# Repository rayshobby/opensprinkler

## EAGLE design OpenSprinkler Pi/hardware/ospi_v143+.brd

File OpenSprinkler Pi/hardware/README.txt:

OpenSprinkler Pi (OSPi) Eagle Design Files
==========================================
Note: requires Eagle CAD v6.0 or above

Part lists of all versions can be found at:
http://goo.gl/4Nrvb

Release Notes
=============
New in v1.43+
* Removed on-board relay. Replaced by a header for RF transmitter.
* Added PCB spark gaps.
* Added laser cut acrylic enclosure design (in EagleCAD file, this is
  at layer 113. A .ai file is also provided).

New in v1.4 / v1.4 B+
* New layout to fit the OpenSprinkler injection-molded enclosure
* Changed on-board relay to 250V / 3A type

New in v1.3
* Added per-station bidirectional TVS (SMBJ48CA)
* Added 2A solder-on fuse
* Added on-board mini-relay (120V / 2A)
* Added rain sensor terminal
* 24V AC terminal block changed to orange 3.96 spacing type

New in v1.2
* Added PCF8591T 8-bit 4-channel ADC (analog-digital converter)
* Added pin headers for ADC and also i2C pins.

New in v1.1
-----------
* Adopt LM2596S-5.0 as switching regulator, less peripheral elements, more output current.
* Improved locations of the separation pillars to fit both RPi rev. 1 and rev. 2.
  There are now two pillars that match the screw hole locations on rev. 2 .
* Changed 32.768kHz crystal to SMT package.
* Changed the value of D1 to S1B type.

Original Release v1.0
---------------------
- MC34063 switching regulator.
- DS1307 RTC with CR1220 backup battery.
- Shift register, BT1308W triac solenoid driver.

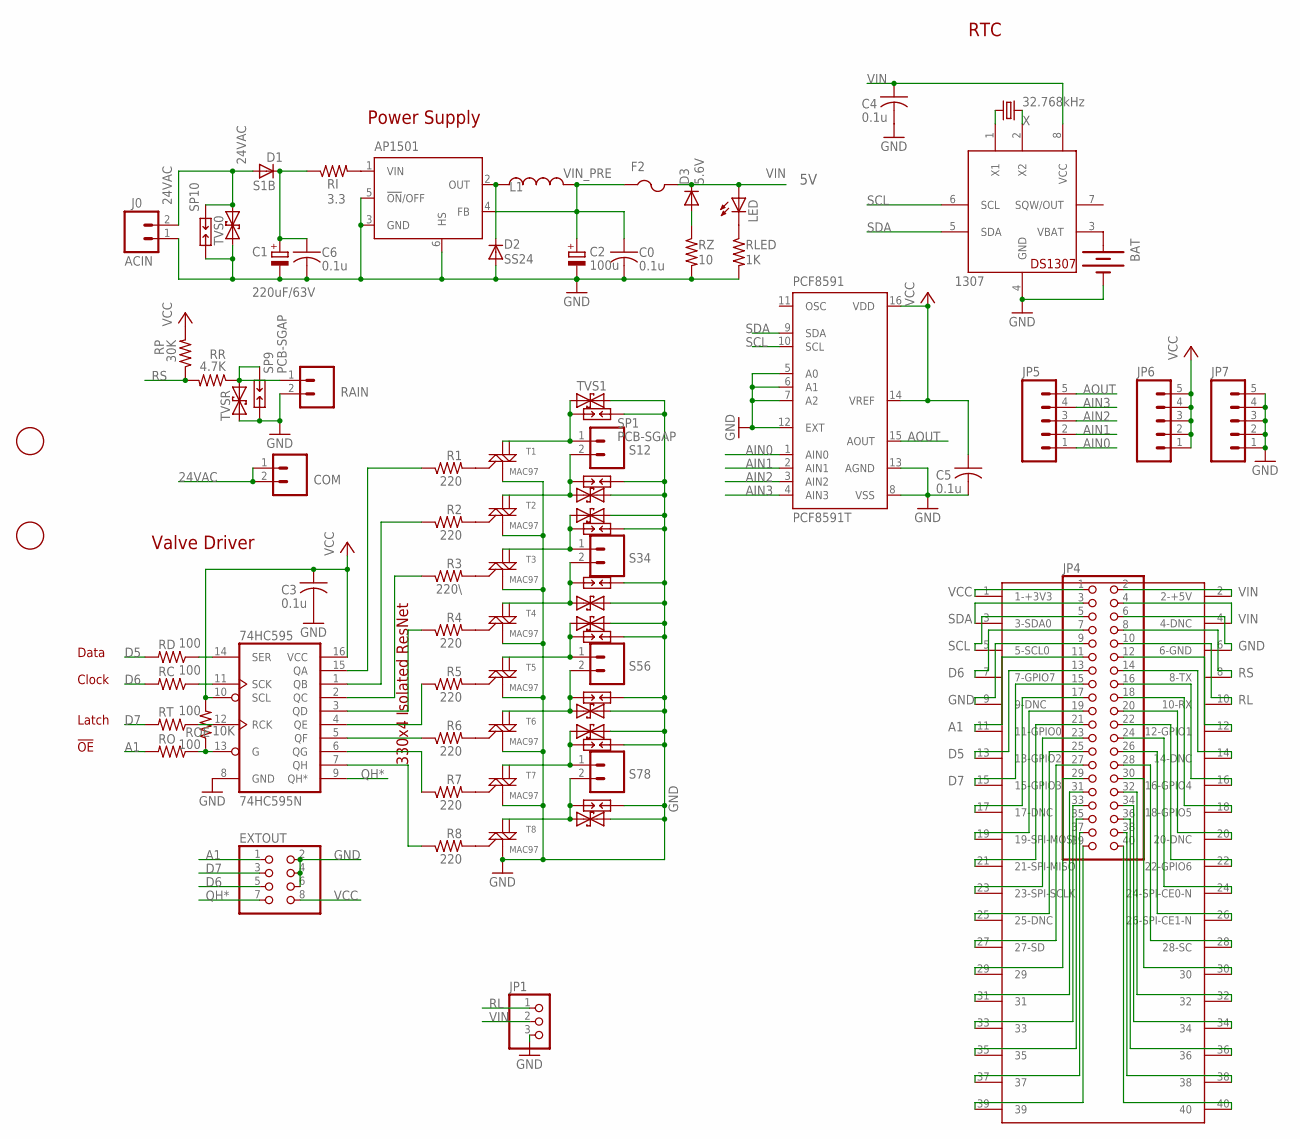
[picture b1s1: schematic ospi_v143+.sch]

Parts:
74HC595: 74HC595N; SO16
1307: DS1307; SO08
AP1501: LM2596S; TO263-5
BAT: BATTERYBATTERY_12MM_SMT; BATTCON_12MM_SMT
C0, C3, C4, C5, C6: 0.1u; C0603K
C1: 220uF/63V; PANASONIC_E
C2: 100u; PANASONIC_E
COM: M025MM-X; SCREWTERMINAL-5MM-2-X
D1: S1B; DO-214AC
D2: SS24; SMB
D3: 5.6V; MINIMELF
EXTOUT: PINHD-2X4/90; 2X04/90
F2: PTCFUSE-1812; 1812
J0: ACIN; SCREWTERMINAL-4MM-2-X
JP1: PINHD-1X3; 1X03
JP4: PINHD-2X20; 2X20
JP5, JP6, JP7: M05PTH; 1X05
L1: 150uH; CDRH125
LED: LEDCHIPLED_0805; CHIPLED_0805
PCF8591: PCF8591T; SO16W
R1, R2, R4, R5, R6, R7, R8: 220; R0603
R3: 220\; R0603
RAIN: M025MM-X; SCREWTERMINAL-5MM-2-X
RC: 100; R0603
RD: 100; R0603
RI: 3.3; R2010
RLED: 1K; R0805
RO: 100; R0603
ROE: 10K; R0603
RP: 30K; R0805
RR: 4.7K; R0805
RT: 100; R0603
RZ: 10; R2010
S12, S34, S56, S78: M025MM-X; SCREWTERMINAL-5MM-2-X
SP1, SP2, SP3, SP4, SP5, SP6, SP7, SP8, SP9, SP10: PCB-SGAP
T1, T2, T3, T4, T5, T6, T7, T8: MAC97; SOT223
TVS0, TVS1, TVS2, TVS3, TVS4, TVS5, TVS6, TVS7, TVS8: TVSSMB; SMB
TVSR: TVSSMB; SMB
U$1, U$3: FIDUCIAL; FIDUCIAL_1MM
U$2: RPIB+
X: 32.768kHz; MM20SS

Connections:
24VAC: COM.1, COM.2, D1.A, J0.2, SP10.1, TVS0.C
A1: EXTOUT.1, JP4.11, RO.2, U$2.11 (11-GPIO0)
AIN0: JP5.1, PCF8591.1 (AIN0)
AIN1: JP5.2, PCF8591.2 (AIN1)
AIN2: JP5.3, PCF8591.3 (AIN2)
AIN3: JP5.4, PCF8591.4 (AIN3)
AOUT: JP5.5, PCF8591.15 (AOUT)
D5: JP4.13, RD.2, U$2.13 (13-GPIO2)
D6: EXTOUT.5, JP4.7, RC.2, U$2.7 (7-GPIO7)
D7: EXTOUT.3, JP4.15, RT.2, U$2.15 (15-GPIO3)
GND: 74HC595.8 (GND), 1307.4 (GND), AP1501.3 (GND), AP1501.5 (!ON!/OFF), AP1501.6 (HS), BAT.P$1 (-), C0.2, C1.-, C2.-, C3.2, C4.2, C5.2, C6.2, D2.A, EXTOUT.2, EXTOUT.4, EXTOUT.6, J0.1, JP1.3, JP4.6, JP4.9, JP7.1, JP7.2, JP7.3, JP7.4, JP7.5, PCF8591.5 (A0), PCF8591.6 (A1), PCF8591.7 (A2), PCF8591.8 (VSS), PCF8591.12 (EXT), PCF8591.13 (AGND), RAIN.2, RLED.2, RZ.2, SP1.1, SP2.1, SP3.1, SP4.1, SP5.1, SP6.1, SP7.1, SP8.1, SP9.2, SP10.2, T1.1 (M1), T2.1 (M1), T3.1 (M1), T4.1 (M1), T5.1 (M1), T6.1 (M1), T7.1 (M1), T8.1 (M1), TVS0.A, TVS1.C, TVS2.C, TVS3.C, TVS4.C, TVS5.C, TVS6.C, TVS7.C, TVS8.C, TVSR.A, U$2.6 (6-GND), U$2.9 (9-DNC)
unnamed: LED.C, RLED.1
unnamed: C1.+, C6.1, D1.C, RI.1
unnamed: R1.2, T1.3 (G)
unnamed: 74HC595.5 (QF), R6.1
unnamed: 74HC595.6 (QG), R7.1
unnamed: D3.A, RZ.1
unnamed: 74HC595.7 (QH), R8.1
unnamed: AP1501.2 (OUT), D2.C, L1.1
unnamed: 1307.2 (X2), X.4 (2)
unnamed: 74HC595.4 (QE), R5.1
unnamed: 74HC595.3 (QD), R4.1
unnamed: 74HC595.2 (QC), R3.1
unnamed: 74HC595.1 (QB), R2.1
unnamed: 74HC595.15 (QA), R1.1
unnamed: R2.2, T2.3 (G)
unnamed: S12.1, SP1.2, T1.2 (M2), TVS1.A
unnamed: S12.2, SP2.2, T2.2 (M2), TVS2.A
unnamed: S34.1, SP3.2, T3.2 (M2), TVS3.A
unnamed: R3.2, T3.3 (G)
unnamed: S34.2, SP4.2, T4.2 (M2), TVS4.A
unnamed: R4.2, T4.3 (G)
unnamed: S56.1, SP5.2, T5.2 (M2), TVS5.A
unnamed: S56.2, SP6.2, T6.2 (M2), TVS6.A
unnamed: S78.1, SP7.2, T7.2 (M2), TVS7.A
unnamed: S78.2, SP8.2, T8.2 (M2), TVS8.A
unnamed: R5.2, T5.3 (G)
unnamed: R6.2, T6.3 (G)
unnamed: R7.2, T7.3 (G)
unnamed: R8.2, T8.3 (G)
unnamed: 1307.1 (X1), X.1
unnamed: RAIN.1, RR.1, SP9.1, TVSR.C
unnamed: 74HC595.14 (SER), RD.1
unnamed: 74HC595.11 (SCK), RC.1
unnamed: 74HC595.12 (RCK), RT.1
unnamed: 1307.3 (VBAT), BAT.P$2 (+)
unnamed: JP4.12, U$2.12 (12-GPIO1)
unnamed: JP4.14, U$2.14 (14-DNC)
unnamed: JP4.16, U$2.16 (16-GPIO4)
unnamed: 74HC595.13 (G), RO.1, ROE.1
unnamed: JP4.23, U$2.23 (23-SPI-SCLK)
unnamed: JP4.25, U$2.25 (25-DNC)
unnamed: JP4.27, U$2.27 (27-SD)
unnamed: JP4.29, U$2.29
unnamed: JP4.39, U$2.39
unnamed: JP4.37, U$2.37
unnamed: JP4.17, U$2.17 (17-DNC)
unnamed: JP4.19, U$2.19 (19-SPI-MOSI)
unnamed: JP4.21, U$2.21 (21-SPI-MISO)
unnamed: JP4.35, U$2.35
unnamed: JP4.33, U$2.33
unnamed: JP4.31, U$2.31
unnamed: JP4.34, U$2.34
unnamed: JP4.36, U$2.36
unnamed: JP4.38, U$2.38
unnamed: JP4.40, U$2.40
unnamed: AP1501.1 (VIN), RI.2
unnamed: JP4.18, U$2.18 (18-GPIO5)
unnamed: JP4.20, U$2.20 (20-DNC)
unnamed: JP4.22, U$2.22 (22-GPIO6)
unnamed: JP4.24, U$2.24 (24-SPI-CE0-N)
unnamed: JP4.26, U$2.26 (26-SPI-CE1-N)
unnamed: JP4.28, U$2.28 (28-SC)
unnamed: JP4.30, U$2.30
unnamed: JP4.32, U$2.32
QH*: 74HC595.9 (QH*), EXTOUT.7
RL: JP1.1, JP4.10, U$2.10 (10-RX)
RS: JP4.8, RP.1, RR.2, U$2.8 (8-TX)
SCL: 1307.6 (SCL), JP4.5, PCF8591.10 (SCL), U$2.5 (5-SCL0)
SDA: 1307.5 (SDA), JP4.3, PCF8591.9 (SDA), U$2.3 (3-SDA0)
VCC: 74HC595.10 (SCL), 74HC595.16 (VCC), C3.1, C5.1, EXTOUT.8, JP4.1, JP6.1, JP6.2, JP6.3, JP6.4, JP6.5, PCF8591.14 (VREF), PCF8591.16 (VDD), ROE.2, RP.2, U$2.1 (1-+3V3)
VIN: 1307.8 (VCC), C4.1, D3.C, F2.2, JP1.2, JP4.2, JP4.4, LED.A, U$2.2 (2-+5V), U$2.4 (4-DNC)
VIN_PRE: AP1501.4 (FB), C0.1, C2.+, F2.1, L1.2

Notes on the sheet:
Power Supply
Valve Driver
Data
Clock
Latch
330x4 Isolated ResNet
!OE
RTC

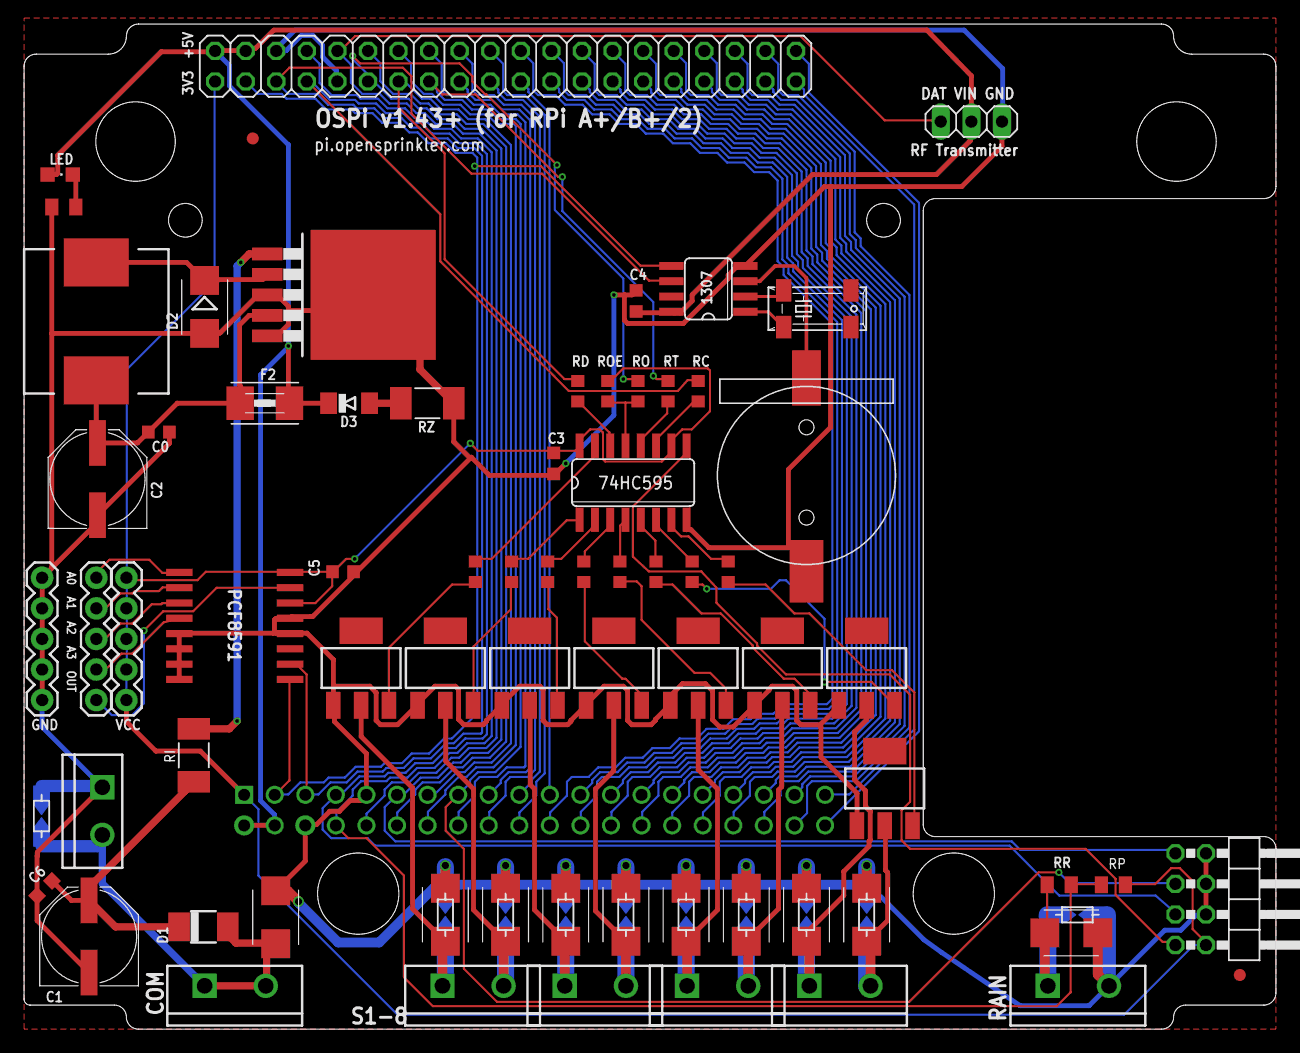
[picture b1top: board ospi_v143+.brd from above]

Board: 2 copper layers, 104.0 x 83.5 mm, 81 parts (1 on the bottom side), 83 nets.

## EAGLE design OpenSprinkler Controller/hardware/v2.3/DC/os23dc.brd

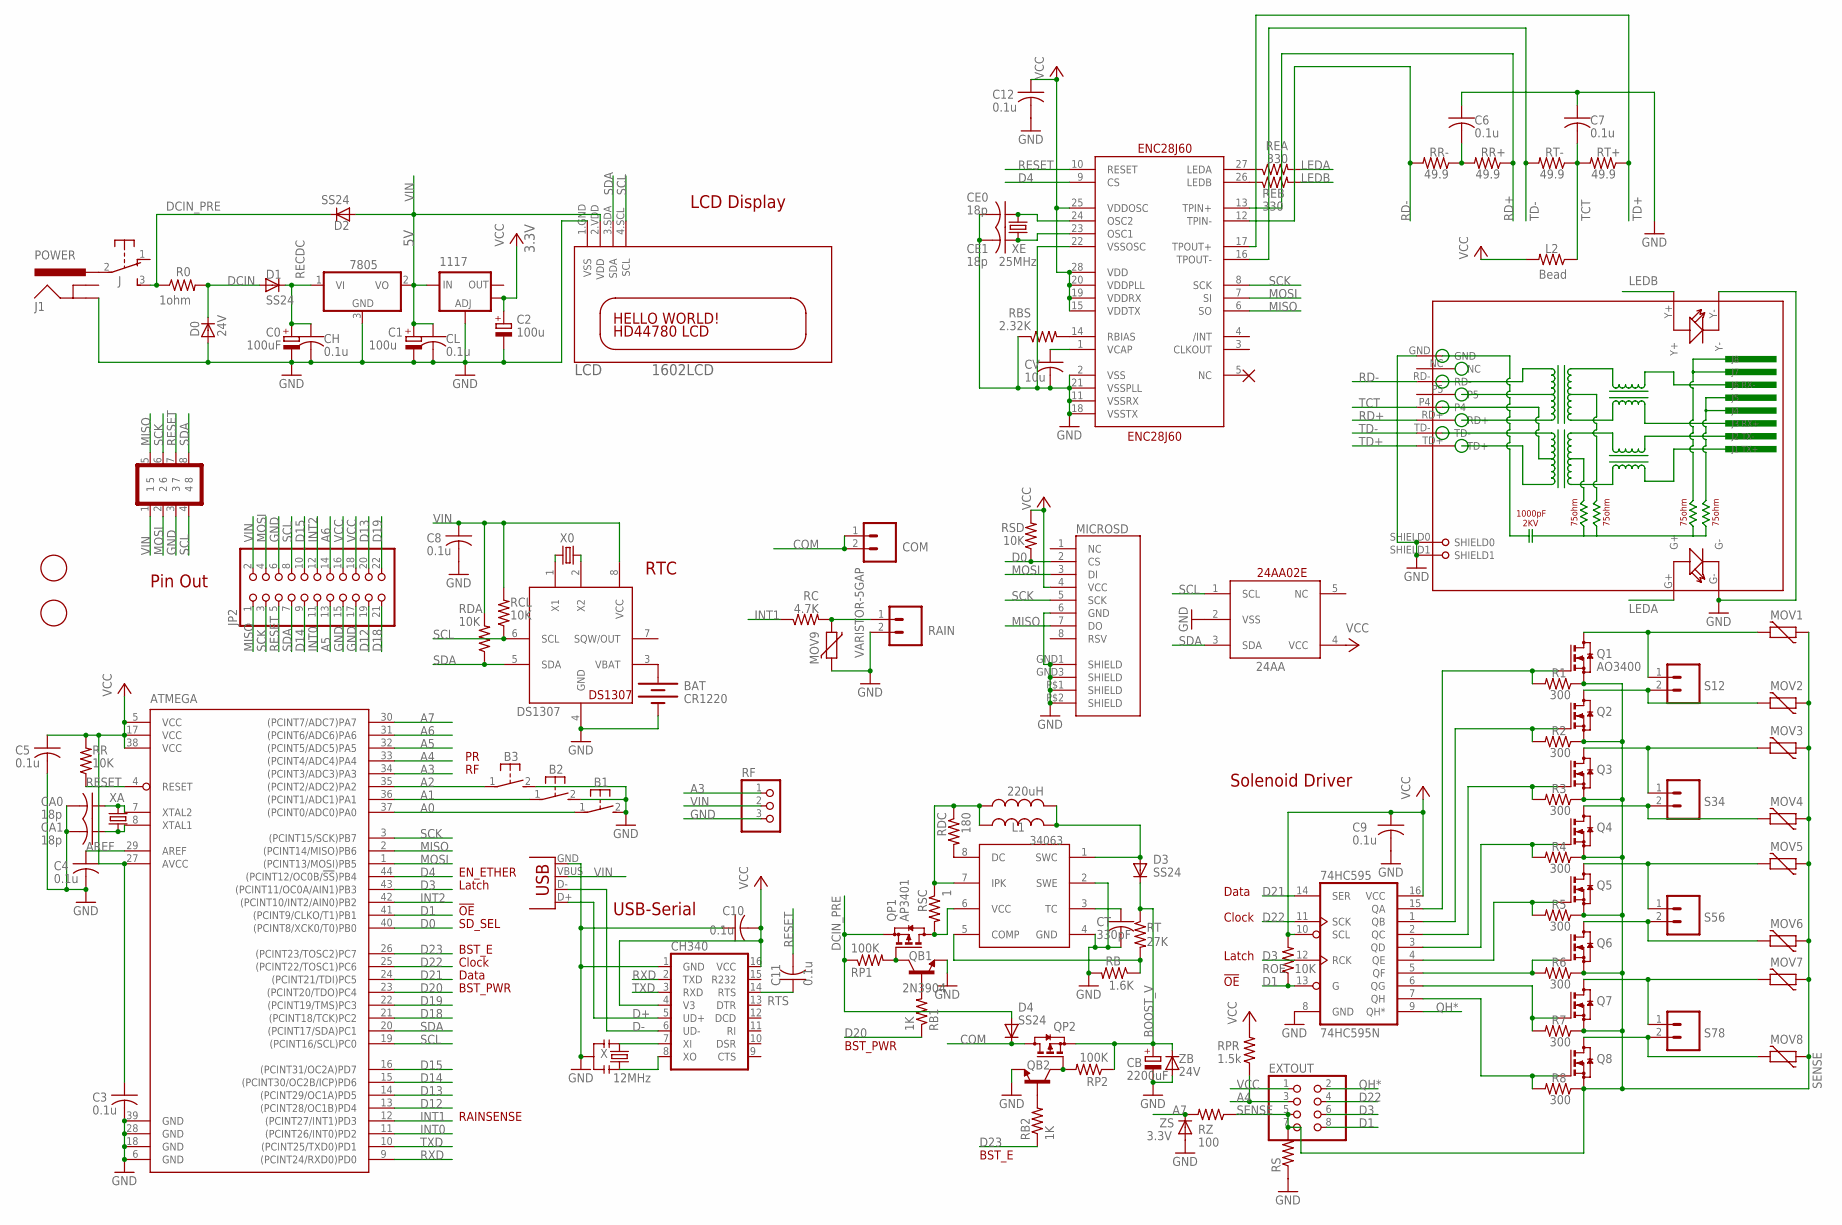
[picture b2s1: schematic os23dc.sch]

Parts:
24AA: 24AA02E48; SOT23-5L
74HC595: 74HC595N; SO16
1117: V_REG_LM1117SOT223; SOT223
7805: 7805DT; TO252
34063: MC33063/MC34063D; SO08
ATMEGA: ATMEGA644A; TQFP44
B1, B2, B3: 31-XX; B3F-31XX
BAT: CR1220; BATTCON_12MM_SMT
C0: 100uF; PANASONIC_E
C1, C2: 100u; PANASONIC_D
C3, C7: 0.1u; C0603K
C4, C5, C6, C8, C9, C10, C11, C12: 0.1u; C0603
CA0, CA1: 18p; C0603K
CB: 2200uF; E7,5-16
CE0, CE1: 18p; C0603K
CH: 0.1u; C0603
CH340: CH340G; SO16
CL: 0.1u; C0603
COM: M025MM-X; SCREWTERMINAL-5MM-2-X
CT: 330pF; C0603K
CV: 10u; C0805K
D0: 24V; MINIMELF
D1, D2, D3, D4: SS24; DO-214AC
DS1307: DS1307; SO08
ENC28J60: ENC28J60; SSOP28DB
EXTOUT: PINHD-2X4; 2X04
J: EG1206
J1: POWER; POWER_JACK_PTH_LOCK
JP2: PINHD-2X11; 2X11
L1: INDUCTORCR54; CR54
L1': 220uH; 0204/5
L2: Bead; R0805
LCD: 1602LCD; LCD1602-I2C-SIDE
MICROSD: USD-SOCKETMICRO-SD-SOCKET-TAOBAO; MICRO-SD-SOCKET-TAOBAO
MOV1, MOV2, MOV3, MOV4, MOV5, MOV6, MOV7, MOV8: 7D270K; R-5GAP
MOV9: VARISTOR-5GAP; R-5GAP
Q1: AO3400; SOT23
Q2, Q3, Q4, Q5, Q6, Q7, Q8: BSS123; SOT23
QB1: 2N3904; SOT23-3
QB2: TRANSISTOR_NPNSOT23-3; SOT23-3
QP1: AP3401; SOT23
QP2: BSS84; SOT23
R0: 1ohm; R2010
R1, R2, R3, R4, R5, R6, R7, R8: 300; R0603
RAIN: M025MM-X; SCREWTERMINAL-5MM-2-X
RB: 1.6K; R0603
RB1, RB2: 1K; R0603
RBS: 2.32K; R0805
RC: 4.7K; R0805
RCL: 10K; R0603
RDA: 10K; R0603
RDC: 180; R0603
REA: 330; R0603
REB: 330; R0603
RF: PINHD-1X3; 1X03
RJ45: HR911105A
ROE: 10K; R0603
RP1, RP2: 100K; R0603
RPR: 1.5k; R0603
RR: 10K; R0603
RR+: 49.9; R0603
RR-: 49.9; R0603
RS: R-US_R2512; R2512
RSC: 1; R0603
RSD: 10K; R0603
RT: 27K; R0603
RT+: 49.9; R0603
RT-: 49.9; R0603
RZ: 100; R0402
S12, S34, S56, S78: M025MM-X; SCREWTERMINAL-5MM-2-X
U$1, U$3: FIDUCIAL; FIDUCIAL_1MM
U$4: GOLDFINGER_2X4
USB: USBPTH; USB-B-PTH
X: 12MHz; RESONATOR-SMD
X0: 32.768kHz; MM20SS
XA: 12MHz; 4SMD
XE: 25MHz; 4SMD
ZB: 24V; MINIMELF
ZS: 3.3V; MINIMELF

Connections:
A0: ATMEGA.37 ((PCINT0/ADC0)PA0), B1.1
A1: ATMEGA.36 ((PCINT1/ADC1)PA1), B2.1
A2: ATMEGA.35 ((PCINT2/ADC2)PA2), B3.1
A3: ATMEGA.34 ((PCINT3/ADC3)PA3), RF.1
A4: ATMEGA.33 ((PCINT4/ADC4)PA4), EXTOUT.3, RPR.1
A5: ATMEGA.32 ((PCINT5/ADC5)PA5), JP2.13
A6: ATMEGA.31 ((PCINT6/ADC6)PA6), JP2.14
A7: ATMEGA.30 ((PCINT7/ADC7)PA7), RZ.2, ZS.C
AREF: ATMEGA.29 (AREF), C4.1
BOOST_V: CB.+, D3.C, QP2.2 (S), RP2.1, RT.1, ZB.C
COM: COM.1, COM.2, D4.C, QP2.3 (D)
D0: ATMEGA.40 ((PCINT8/XCK0/T0)PB0), MICROSD.2 (CS), RSD.1
D1: 74HC595.13 (G), ATMEGA.41 ((PCINT9/CLKO/T1)PB1), EXTOUT.8, ROE.1
D3: 74HC595.12 (RCK), ATMEGA.43 ((PCINT11/OC0A/AIN1)PB3), EXTOUT.6
D4: ATMEGA.44 ((PCINT12/OC0B/!SS!)PB4), ENC28J60.9 (CS)
D12: ATMEGA.13 ((PCINT28/OC1B)PD4), JP2.19
D13: ATMEGA.14 ((PCINT29/OC1A)PD5), JP2.20
D14: ATMEGA.15 ((PCINT30/OC2B/ICP)PD6), JP2.9
D15: ATMEGA.16 ((PCINT31/OC2A)PD7), JP2.10
D18: ATMEGA.21 ((PCINT18/TCK)PC2), JP2.21
D19: ATMEGA.22 ((PCINT19/TMS)PC3), JP2.22
D20: ATMEGA.23 ((PCINT20/TDO)PC4), RB1.1
D21: 74HC595.14 (SER), ATMEGA.24 ((PCINT21/TDI)PC5)
D22: 74HC595.11 (SCK), ATMEGA.25 ((PCINT22/TOSC1)PC6), EXTOUT.4
D23: ATMEGA.26 ((PCINT23/TOSC2)PC7), RB2.1
D+: CH340.5 (UD+), USB.D+
D-: CH340.6 (UD-), USB.D-
DCIN: D0.C, D1.A, R0.2
DCIN_PRE: D2.C, D4.A, J.3 (S), QP1.2 (S), R0.1, RP1.1
GND: 24AA.2 (VSS), 74HC595.8 (GND), 1117.1 (ADJ), 7805.3 (GND), 34063.2 (SWE), 34063.4 (GND), ATMEGA.6 (GND), ATMEGA.18 (GND), ATMEGA.28 (GND), ATMEGA.39 (GND), B1.2 (S), B2.2 (S), B3.2 (S), BAT.P$1 (-), C0.-, C1.-, C2.-, C3.2, C4.2, C5.2, C6.1, C7.1, C8.2, C9.2, C10.1, C12.2, CA0.2, CA1.2, CB.-, CE0.2, CE1.2, CH.2, CH340.1 (GND), CL.2, CT.2, CV.2, D0.A, DS1307.4 (GND), ENC28J60.2 (VSS), ENC28J60.11 (VSSRX), ENC28J60.18 (VSSTX), ENC28J60.21 (VSSPLL), ENC28J60.22 (VSSOSC), J1.GND, JP2.6, JP2.15, JP2.17, LCD.1.GND (VSS), MICROSD.6 (GND), MICROSD.GND1 (SHIELD), MICROSD.GND3 (SHIELD), MICROSD.P$1 (SHIELD), MICROSD.P$2 (SHIELD), MOV9.2, QB1.2 (E), QB2.2 (E), RAIN.2, RB.2, RBS.1, RF.3, RJ45.G-, RJ45.GND, RJ45.SHIELD0, RJ45.SHIELD1, RJ45.Y-, RS.1, U$4.3, USB.GND, X.2, ZB.A, ZS.A
INT0: ATMEGA.11 ((PCINT26/INT0)PD2), JP2.11
INT1: ATMEGA.12 ((PCINT27/INT1)PD3), RC.1
INT2: ATMEGA.42 ((PCINT10/INT2/AIN0)PB2), JP2.12
LEDA: REA.2, RJ45.G+
LEDB: REB.2, RJ45.Y+
MISO: ATMEGA.2 ((PCINT14/MISO)PB6), ENC28J60.6 (SO), JP2.1, MICROSD.7 (DO), U$4.5
MOSI: ATMEGA.1 ((PCINT13/MOSI)PB5), ENC28J60.7 (SI), JP2.4, MICROSD.3 (DI), U$4.2
unnamed: J.2, J1.PWR
unnamed: QB1.3 (C), QP1.1 (G), RP1.2
unnamed: MOV9.1, RAIN.1, RC.2
unnamed: 74HC595.5 (QF), Q6.1 (G), R6.2
unnamed: 74HC595.6 (QG), Q7.1 (G), R7.2
unnamed: CH340.7 (XI), X.1
unnamed: 74HC595.7 (QH), Q8.1 (G), R8.2
unnamed: DS1307.1 (X1), X0.1
unnamed: 34063.1 (SWC), D3.A, L1.P$2 (2), L1'.2
unnamed: 74HC595.4 (QE), Q5.1 (G), R5.2
unnamed: 74HC595.3 (QD), Q4.1 (G), R4.2
unnamed: 74HC595.2 (QC), Q3.1 (G), R3.2
unnamed: 74HC595.1 (QB), Q2.1 (G), R2.2
unnamed: 74HC595.15 (QA), Q1.1 (G), R1.2
unnamed: ATMEGA.7 (XTAL2), CA0.1, XA.1
unnamed: MOV1.2, Q1.3 (D), S12.1
unnamed: MOV2.2, Q2.3 (D), S12.2
unnamed: MOV3.2, Q3.3 (D), S34.1
unnamed: ATMEGA.8 (XTAL1), CA1.1, XA.3 (2)
unnamed: MOV4.2, Q4.3 (D), S34.2
unnamed: MOV5.2, Q5.3 (D), S56.1
unnamed: MOV6.2, Q6.3 (D), S56.2
unnamed: MOV7.2, Q7.3 (D), S78.1
unnamed: MOV8.2, Q8.3 (D), S78.2
unnamed: 34063.7 (IPK), L1.P$1 (1), L1'.1, RDC.1, RSC.1
unnamed: 34063.6 (VCC), QP1.3 (D), RSC.2
unnamed: 34063.3 (TC), CT.1
unnamed: 34063.5 (COMP), RB.1, RT.2
unnamed: DS1307.2 (X2), X0.4 (2)
unnamed: 34063.8 (DC), RDC.2
unnamed: QB1.1 (B), RB1.2
unnamed: ENC28J60.27 (LEDA), REA.1
unnamed: BAT.P$2 (+), DS1307.3 (VBAT)
unnamed: ENC28J60.26 (LEDB), REB.1
unnamed: QB2.3 (C), QP2.1 (G), RP2.2
unnamed: CV.1, ENC28J60.1 (VCAP)
unnamed: CH340.8 (XO), X.3
unnamed: CE0.1, ENC28J60.24 (OSC2), XE.3 (2)
unnamed: CE1.1, ENC28J60.23 (OSC1), XE.1
unnamed: QB2.1 (B), RB2.2
unnamed: C6.2, RR+.2, RR-.1
unnamed: ENC28J60.14 (RBIAS), RBS.2
QH*: 74HC595.9 (QH*), EXTOUT.2
RD+: ENC28J60.13 (TPIN+), RJ45.RD+, RR+.1
RD-: ENC28J60.12 (TPIN-), RJ45.RD-, RR-.2
RECDC: 7805.1 (VI), C0.+, CH.1, D1.C
RESET: ATMEGA.4 (RESET), C11.2, ENC28J60.10 (RESET), JP2.5, RR.1, U$4.7
RTS: C11.1, CH340.14 (RTS)
RXD: ATMEGA.9 ((PCINT24/RXD0)PD0), CH340.2 (TXD)
SCK: ATMEGA.3 ((PCINT15/SCK)PB7), ENC28J60.8 (SCK), JP2.3, MICROSD.5 (SCK), U$4.6
SCL: 24AA.1 (SCL), ATMEGA.19 ((PCINT16/SCL)PC0), DS1307.6 (SCL), JP2.8, LCD.4.SCL (SCL), RCL.1, U$4.4
SDA: 24AA.3 (SDA), ATMEGA.20 ((PCINT17/SDA)PC1), DS1307.5 (SDA), JP2.7, LCD.3.SDA (SDA), RDA.1, U$4.8
SENSE: EXTOUT.5, EXTOUT.7, MOV1.1, MOV2.1, MOV3.1, MOV4.1, MOV5.1, MOV6.1, MOV7.1, MOV8.1, Q1.2 (S), Q2.2 (S), Q3.2 (S), Q4.2 (S), Q5.2 (S), Q6.2 (S), Q7.2 (S), Q8.2 (S), R1.1, R2.1, R3.1, R4.1, R5.1, R6.1, R7.1, R8.1, RS.2, RZ.1
TCT: C7.2, L2.1, RJ45.P4, RT+.2, RT-.1
TD+: ENC28J60.17 (TPOUT+), RJ45.TD+, RT+.1
TD-: ENC28J60.16 (TPOUT-), RJ45.TD-, RT-.2
TXD: ATMEGA.10 ((PCINT25/TXD0)PD1), CH340.3 (RXD)
VCC: 24AA.4 (VCC), 74HC595.10 (SCL), 74HC595.16 (VCC), 1117.4 (OUT), ATMEGA.5 (VCC), ATMEGA.17 (VCC), ATMEGA.27 (AVCC), ATMEGA.38 (VCC), C2.+, C3.1, C5.1, C9.1, C10.2, C12.1, CH340.4 (V3), CH340.16 (VCC), ENC28J60.15 (VDDTX), ENC28J60.19 (VDDRX), ENC28J60.20 (VDDPLL), ENC28J60.25 (VDDOSC), ENC28J60.28 (VDD), EXTOUT.1, JP2.16, JP2.18, L2.2, MICROSD.4 (VCC), ROE.2, RPR.2, RR.2, RSD.2
VIN: 1117.3 (IN), 7805.2 (VO), C1.+, C8.1, CL.1, D2.A, DS1307.8 (VCC), JP2.2, LCD.2.VDD (VDD), RCL.2, RDA.2, RF.2, U$4.1, USB.VBUS

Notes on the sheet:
Solenoid Driver
Data
Clock
Latch
EN_ETHER
3.3V
!OE
RAINSENSE
SD_SEL
USB-Serial
Pin Out
RTC
BST_E
BST_PWR
LCD Display

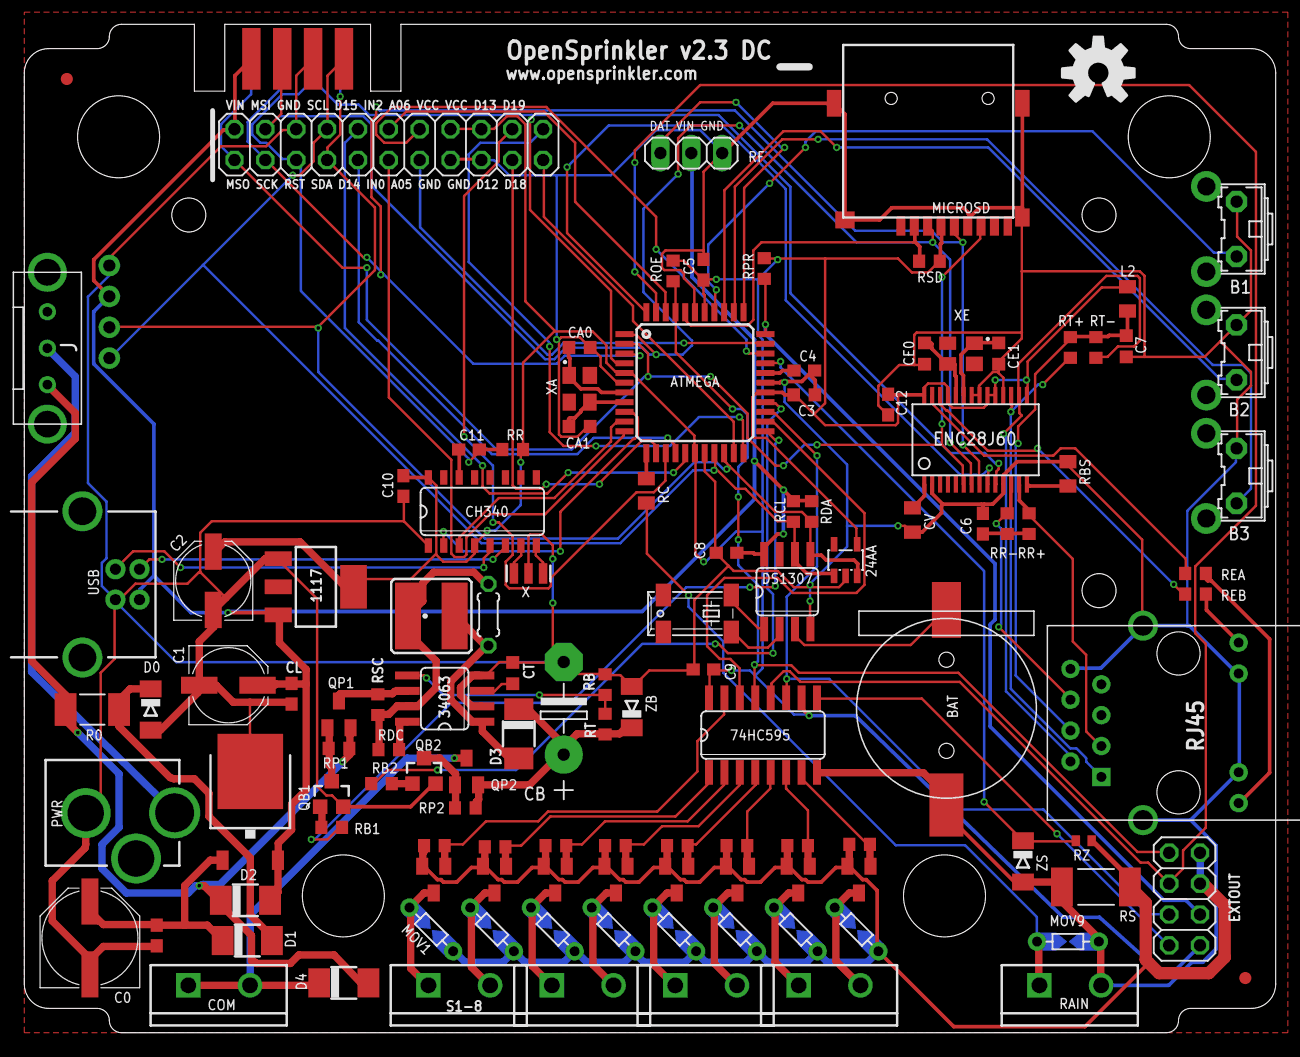
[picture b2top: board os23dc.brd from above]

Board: 2 copper layers, 103.0 x 83.0 mm, 121 parts (0 on the bottom side), 96 nets.

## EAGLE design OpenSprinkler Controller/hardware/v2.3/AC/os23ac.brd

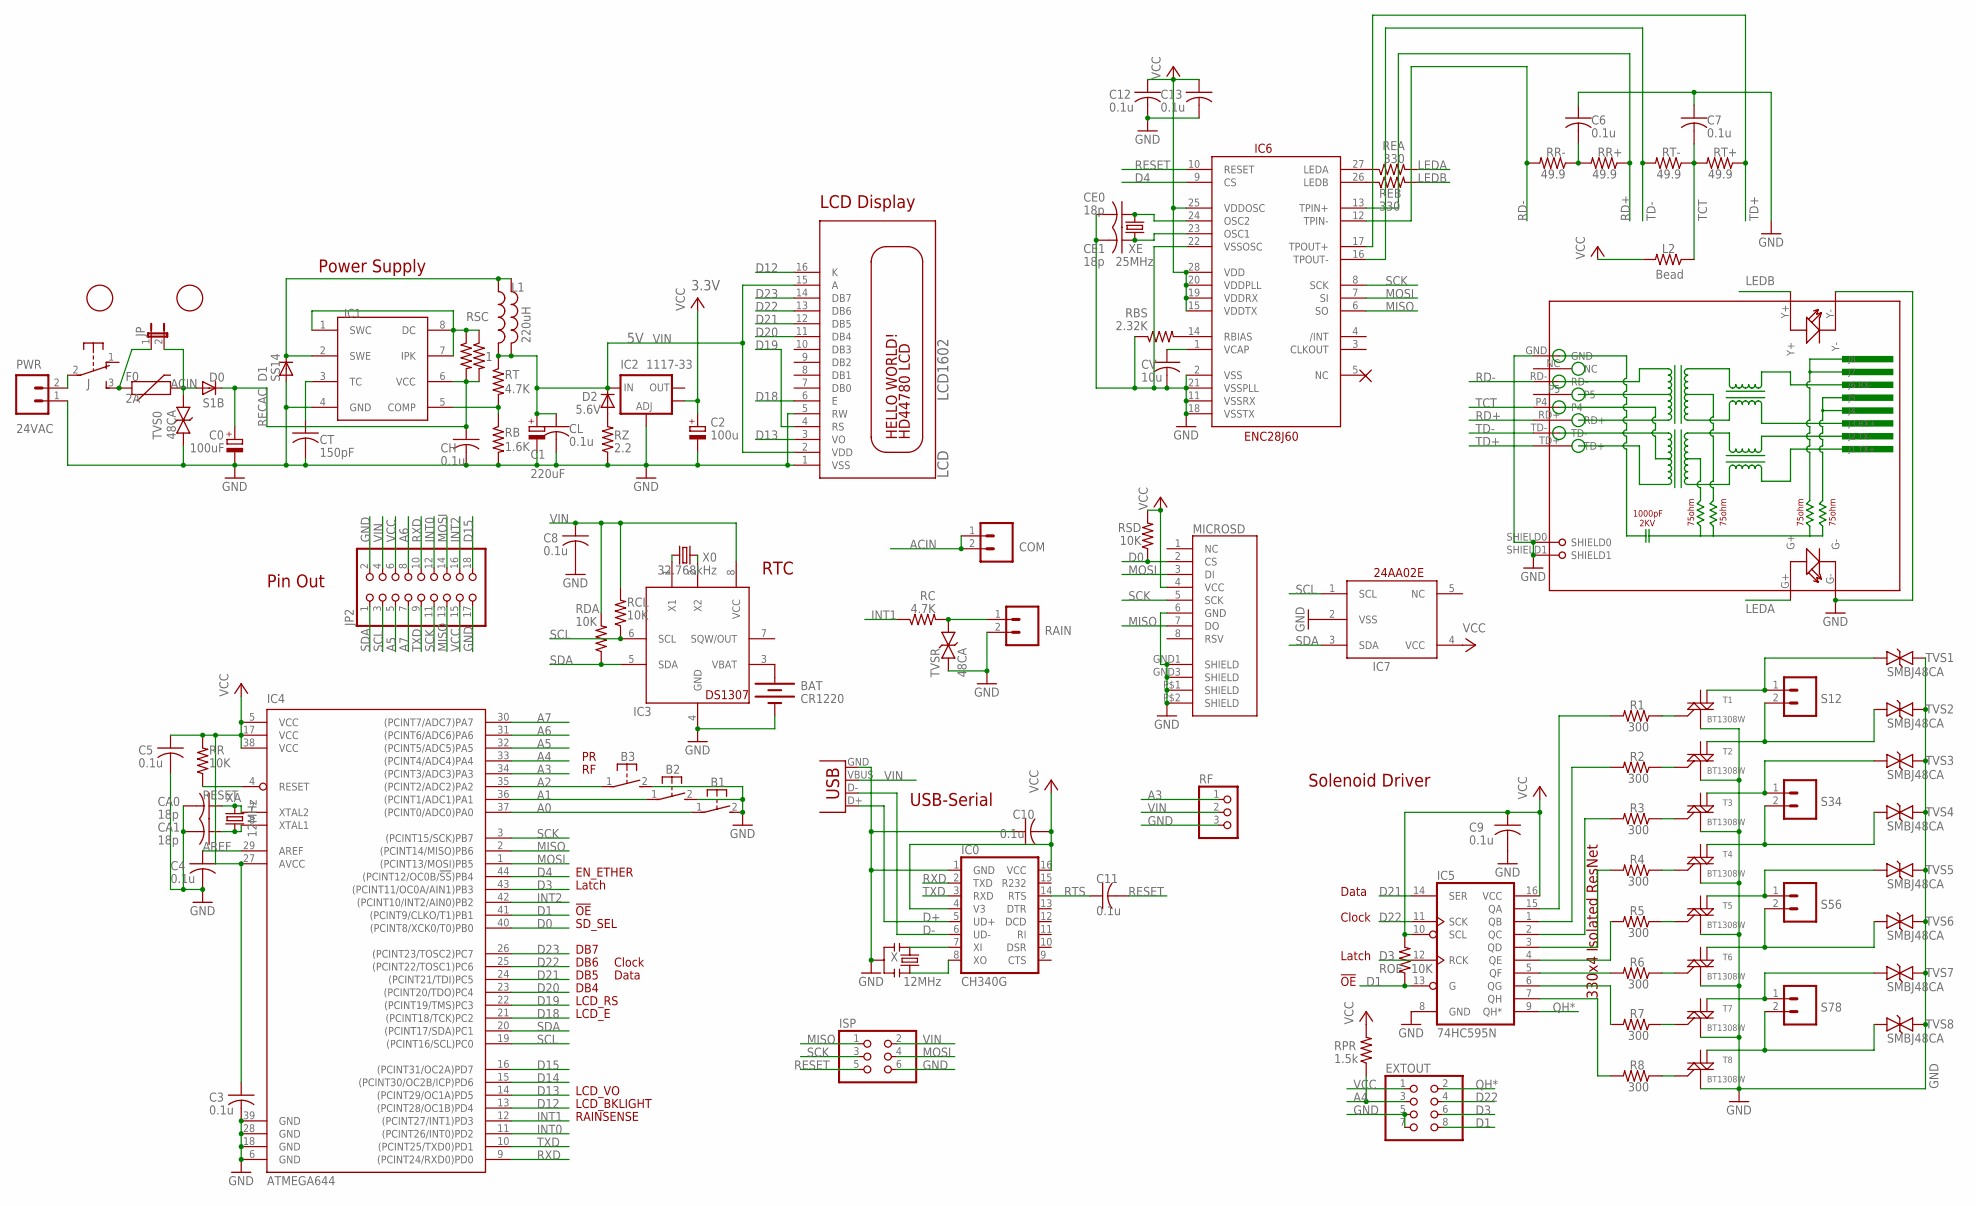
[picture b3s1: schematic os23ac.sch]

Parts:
B1, B2, B3: 31-XX; B3F-31XX
BAT: CR1220; BATTCON_12MM_SMT
C0: 100uF; PANASONIC_E
C1: 220uF; PANASONIC_E
C2: 100u; PANASONIC_D
C3, C7: 0.1u; C0603K
C4, C5, C6, C8, C9, C10, C11, C12, C13: 0.1u; C0603
CA0, CA1: 18p; C0603K
CE0, CE1: 18p; C0603K
CH: 0.1u; C0603
CL: 0.1u; C0603
COM: M025MM-X; SCREWTERMINAL-5MM-2-X
CT: 150pF; C0603K
CV: 10u; C0805K
D0: S1B; DO-214AC
D1: SS14; DO-214AC
D2: 5.6V; MINIMELF
EXTOUT: PINHD-2X4; 2X04
F0: 2A; PTC-1206
IC0: CH340G; SO16
IC1: 34063; SO08
IC2: 1117-33; SOT223
IC3: DS1307; SO08
IC4: ATMEGA644; TQFP44
IC5: 74HC595N; SO16
IC6: ENC28J60; SSOP28DB
IC7: 24AA02E; SOT23-5L
ISP: PINHD-2X3; 2X03
J: EG1206
JP: JUMPER-2PTH; 1X02
JP2: PINHD-2X9-CBIG; 2X09-CLEANBIG
L1: INDUCTORPWR; CDRH125
L1': 220uH; 0204/5
L2: Bead; R0805
LCD: LCD1602; LCD1602A
MICROSD: USD-SOCKETMICRO-SD-SOCKET-TAOBAO; MICRO-SD-SOCKET-TAOBAO
PWR: 24VAC; SCREWTERMINAL-4MM-2-X
R1, R2, R3, R4, R5, R6, R7, R8: 300; R0603
RAIN: M025MM-X; SCREWTERMINAL-5MM-2-X
RB: 1.6K; R0603
RBS: 2.32K; R0805
RC: 4.7K; R0805
RCL: 10K; R0603
RDA: 10K; R0603
REA: 330; R0603
REB: 330; R0603
RF: PINHD-1X3; 1X03
RJ45: HR911105A
ROE: 10K; R0603
RPR: 1.5k; R0603
RR: 10K; R0603
RR+: 49.9; R0603
RR-: 49.9; R0603
RSC, RSC1: 1; R0805
RSD: 10K; R0603
RT: 4.7K; R0805
RT+: 49.9; R0603
RT-: 49.9; R0603
RZ: 2.2; R2010
S12, S34, S56, S78: M025MM-X; SCREWTERMINAL-5MM-2-X
T1, T2, T3, T4, T5, T6, T7, T8: BT1308W; SOT223
TVS0: 48CA; SMB
TVS1, TVS2, TVS3, TVS4, TVS5, TVS6, TVS7, TVS8: SMBJ48CA; SMB
TVSR: 48CA; SMB
U$1, U$3: FIDUCIAL; FIDUCIAL_1MM
USB: USBPTH; USB-B-PTH
X: 12MHz; RESONATOR-SMD
X0: 32.768kHz; MM20SS
XA: 12MHz; 4SMD
XE: 25MHz; 4SMD

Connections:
A0: B1.1, IC4.37 ((PCINT0/ADC0)PA0)
A1: B2.1, IC4.36 ((PCINT1/ADC1)PA1)
A2: B3.1, IC4.35 ((PCINT2/ADC2)PA2)
A3: IC4.34 ((PCINT3/ADC3)PA3), RF.1
A4: EXTOUT.3, IC4.33 ((PCINT4/ADC4)PA4), RPR.1
A5: IC4.32 ((PCINT5/ADC5)PA5), JP2.5
A6: IC4.31 ((PCINT6/ADC6)PA6), JP2.8
A7: IC4.30 ((PCINT7/ADC7)PA7), JP2.7
ACIN: COM.1, COM.2, D0.A, F0.2, JP.2, TVS0.C
AREF: C4.1, IC4.29 (AREF)
D0: IC4.40 ((PCINT8/XCK0/T0)PB0), MICROSD.2 (CS), RSD.1
D1: EXTOUT.8, IC4.41 ((PCINT9/CLKO/T1)PB1), IC5.13 (G), ROE.1
D3: EXTOUT.6, IC4.43 ((PCINT11/OC0A/AIN1)PB3), IC5.12 (RCK)
D4: IC4.44 ((PCINT12/OC0B/!SS!)PB4), IC6.9 (CS)
D12: IC4.13 ((PCINT28/OC1B)PD4), LCD.16 (K)
D13: IC4.14 ((PCINT29/OC1A)PD5), LCD.3 (VO)
D14: IC4.15 ((PCINT30/OC2B/ICP)PD6)
D15: IC4.16 ((PCINT31/OC2A)PD7), JP2.18
D18: IC4.21 ((PCINT18/TCK)PC2), LCD.6 (E)
D19: IC4.22 ((PCINT19/TMS)PC3), LCD.4 (RS)
D20: IC4.23 ((PCINT20/TDO)PC4), LCD.11 (DB4)
D21: IC4.24 ((PCINT21/TDI)PC5), IC5.14 (SER), LCD.12 (DB5)
D22: EXTOUT.4, IC4.25 ((PCINT22/TOSC1)PC6), IC5.11 (SCK), LCD.13 (DB6)
D23: IC4.26 ((PCINT23/TOSC2)PC7), LCD.14 (DB7)
D+: IC0.5 (UD+), USB.D+
D-: IC0.6 (UD-), USB.D-
GND: B1.2 (S), B2.2 (S), B3.2 (S), BAT.P$1 (-), C0.-, C1.-, C2.-, C3.2, C4.2, C5.2, C6.1, C7.1, C8.2, C9.2, C10.1, C12.2, C13.2, CA0.2, CA1.2, CE0.2, CE1.2, CH.2, CL.2, CT.2, CV.2, D1.A, EXTOUT.5, EXTOUT.7, IC0.1 (GND), IC1.4 (GND), IC2.1 (ADJ), IC3.4 (GND), IC4.6 (GND), IC4.18 (GND), IC4.28 (GND), IC4.39 (GND), IC5.8 (GND), IC6.2 (VSS), IC6.11 (VSSRX), IC6.18 (VSSTX), IC6.21 (VSSPLL), IC6.22 (VSSOSC), IC7.2 (VSS), ISP.6, JP2.2, JP2.17, LCD.1 (VSS), LCD.5 (RW), MICROSD.6 (GND), MICROSD.GND1 (SHIELD), MICROSD.GND3 (SHIELD), MICROSD.P$1 (SHIELD), MICROSD.P$2 (SHIELD), PWR.1, RAIN.2, RB.2, RBS.1, RF.3, RJ45.G-, RJ45.GND, RJ45.SHIELD0, RJ45.SHIELD1, RJ45.Y-, RZ.1, T1.1 (M1), T2.1 (M1), T3.1 (M1), T4.1 (M1), T5.1 (M1), T6.1 (M1), T7.1 (M1), T8.1 (M1), TVS0.A, TVS1.C, TVS2.C, TVS3.C, TVS4.C, TVS5.C, TVS6.C, TVS7.C, TVS8.C, TVSR.A, USB.GND, X.2
INT0: IC4.11 ((PCINT26/INT0)PD2), JP2.12
INT1: IC4.12 ((PCINT27/INT1)PD3), RC.1
INT2: IC4.42 ((PCINT10/INT2/AIN0)PB2), JP2.16
LEDA: REA.2, RJ45.G+
LEDB: REB.2, RJ45.Y+
MISO: IC4.2 ((PCINT14/MISO)PB6), IC6.6 (SO), ISP.1, JP2.13, MICROSD.7 (DO)
MOSI: IC4.1 ((PCINT13/MOSI)PB5), IC6.7 (SI), ISP.4, JP2.14, MICROSD.3 (DI)
unnamed: J.2, PWR.2
unnamed: RAIN.1, RC.2, TVSR.C
unnamed: IC5.5 (QF), R6.2
unnamed: IC5.6 (QG), R7.2
unnamed: IC0.7 (XI), X.1
unnamed: IC5.7 (QH), R8.2
unnamed: IC3.1 (X1), X0.1
unnamed: F0.1, J.3 (S), JP.1
unnamed: IC5.4 (QE), R5.2
unnamed: IC5.3 (QD), R4.2
unnamed: IC5.2 (QC), R3.2
unnamed: IC5.1 (QB), R2.2
unnamed: IC5.15 (QA), R1.2
unnamed: CA0.1, IC4.7 (XTAL2), XA.1
unnamed: S12.1, T1.4 (M2-4), TVS1.A
unnamed: S12.2, T2.4 (M2-4), TVS2.A
unnamed: S34.1, T3.4 (M2-4), TVS3.A
unnamed: CA1.1, IC4.8 (XTAL1), XA.3 (2)
unnamed: S34.2, T4.4 (M2-4), TVS4.A
unnamed: R1.1, T1.3 (G)
unnamed: S56.1, T5.4 (M2-4), TVS5.A
unnamed: S56.2, T6.4 (M2-4), TVS6.A
unnamed: S78.1, T7.4 (M2-4), TVS7.A
unnamed: S78.2, T8.4 (M2-4), TVS8.A
unnamed: R2.1, T2.3 (G)
unnamed: R3.1, T3.3 (G)
unnamed: R4.1, T4.3 (G)
unnamed: R5.1, T5.3 (G)
unnamed: IC3.2 (X2), X0.4 (2)
unnamed: R6.1, T6.3 (G)
unnamed: R7.1, T7.3 (G)
unnamed: IC6.27 (LEDA), REA.1
unnamed: R8.1, T8.3 (G)
unnamed: BAT.P$2 (+), IC3.3 (VBAT)
unnamed: IC6.26 (LEDB), REB.1
unnamed: CV.1, IC6.1 (VCAP)
unnamed: IC0.8 (XO), X.3
unnamed: CE0.1, IC6.24 (OSC2), XE.3 (2)
unnamed: CE1.1, IC6.23 (OSC1), XE.1
unnamed: D2.A, RZ.2
unnamed: IC1.1 (SWC), IC1.7 (IPK), IC1.8 (DC), RSC.1, RSC1.1
unnamed: D1.C, IC1.2 (SWE), L1.1, L1'.1
unnamed: CT.1, IC1.3 (TC)
unnamed: C6.2, RR+.2, RR-.1
unnamed: IC1.5 (COMP), RB.1, RT.2
unnamed: IC6.14 (RBIAS), RBS.2
QH*: EXTOUT.2, IC5.9 (QH*)
RD+: IC6.13 (TPIN+), RJ45.RD+, RR+.1
RD-: IC6.12 (TPIN-), RJ45.RD-, RR-.2
RECAC: C0.+, CH.1, D0.C, IC1.6 (VCC), RSC.2, RSC1.2
RESET: C11.2, IC4.4 (RESET), IC6.10 (RESET), ISP.5, RR.1
RTS: C11.1, IC0.14 (RTS)
RXD: IC0.2 (TXD), IC4.9 ((PCINT24/RXD0)PD0), JP2.10
SCK: IC4.3 ((PCINT15/SCK)PB7), IC6.8 (SCK), ISP.3, JP2.11, MICROSD.5 (SCK)
SCL: IC3.6 (SCL), IC4.19 ((PCINT16/SCL)PC0), IC7.1 (SCL), JP2.3, RCL.1
SDA: IC3.5 (SDA), IC4.20 ((PCINT17/SDA)PC1), IC7.3 (SDA), JP2.1, RDA.1
TCT: C7.2, L2.1, RJ45.P4, RT+.2, RT-.1
TD+: IC6.17 (TPOUT+), RJ45.TD+, RT+.1
TD-: IC6.16 (TPOUT-), RJ45.TD-, RT-.2
TXD: IC0.3 (RXD), IC4.10 ((PCINT25/TXD0)PD1), JP2.9
VCC: C2.+, C3.1, C5.1, C9.1, C10.2, C12.1, C13.1, EXTOUT.1, IC0.4 (V3), IC0.16 (VCC), IC2.4 (OUT), IC4.5 (VCC), IC4.17 (VCC), IC4.27 (AVCC), IC4.38 (VCC), IC5.10 (SCL), IC5.16 (VCC), IC6.15 (VDDTX), IC6.19 (VDDRX), IC6.20 (VDDPLL), IC6.25 (VDDOSC), IC6.28 (VDD), IC7.4 (VCC), JP2.6, JP2.15, L2.2, MICROSD.4 (VCC), ROE.2, RPR.2, RR.2, RSD.2
VIN: C1.+, C8.1, CL.1, D2.C, IC2.3 (IN), IC3.8 (VCC), ISP.2, JP2.4, L1.2, L1'.2, LCD.2 (VDD), LCD.15 (A), RCL.2, RDA.2, RF.2, RT.1, USB.VBUS

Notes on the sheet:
Power Supply
Solenoid Driver
Data
Clock
Latch
DB4
330x4 Isolated ResNet
LCD Display
EN_ETHER
3.3V
DB7
LCD_E
LCD_RS
DB6
DB5
!OE
RAINSENSE
LCD_BKLIGHT
LCD_VO
SD_SEL
USB-Serial
Pin Out
RTC

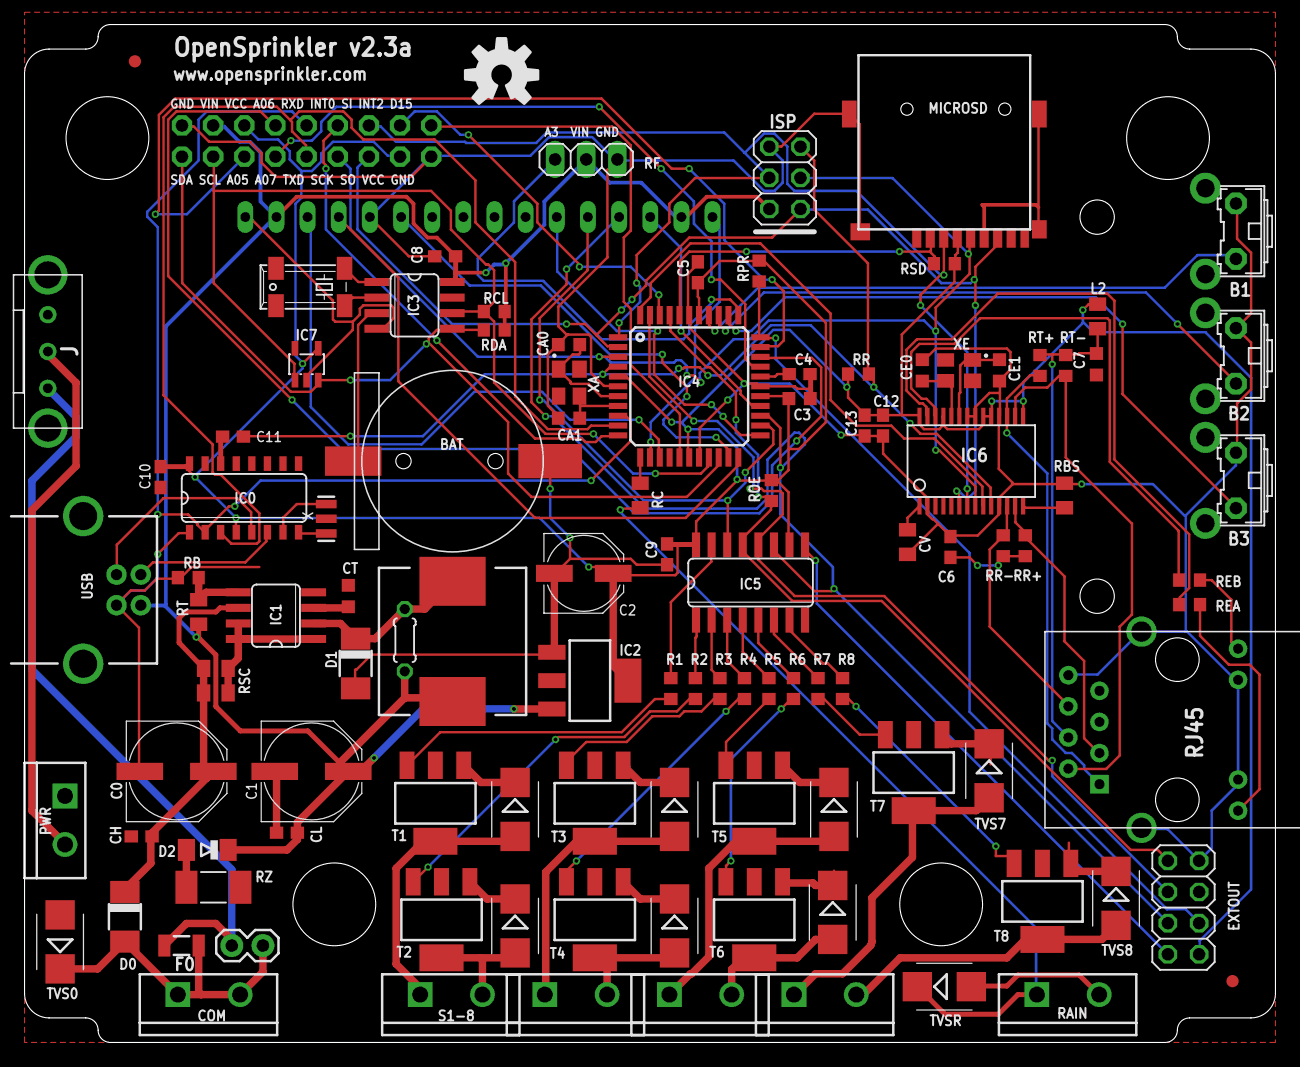
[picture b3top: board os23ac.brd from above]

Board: 2 copper layers, 102.0 x 83.0 mm, 109 parts (0 on the bottom side), 95 nets.

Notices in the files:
parts and their libraries:
SparkFunNew: Licensing: CC v3.0 Share-Alike You are welcome to use this library for commercial purposes.
